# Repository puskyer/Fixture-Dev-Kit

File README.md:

# Fixture-Dev-Kit
A PCB for test fixture prototyping

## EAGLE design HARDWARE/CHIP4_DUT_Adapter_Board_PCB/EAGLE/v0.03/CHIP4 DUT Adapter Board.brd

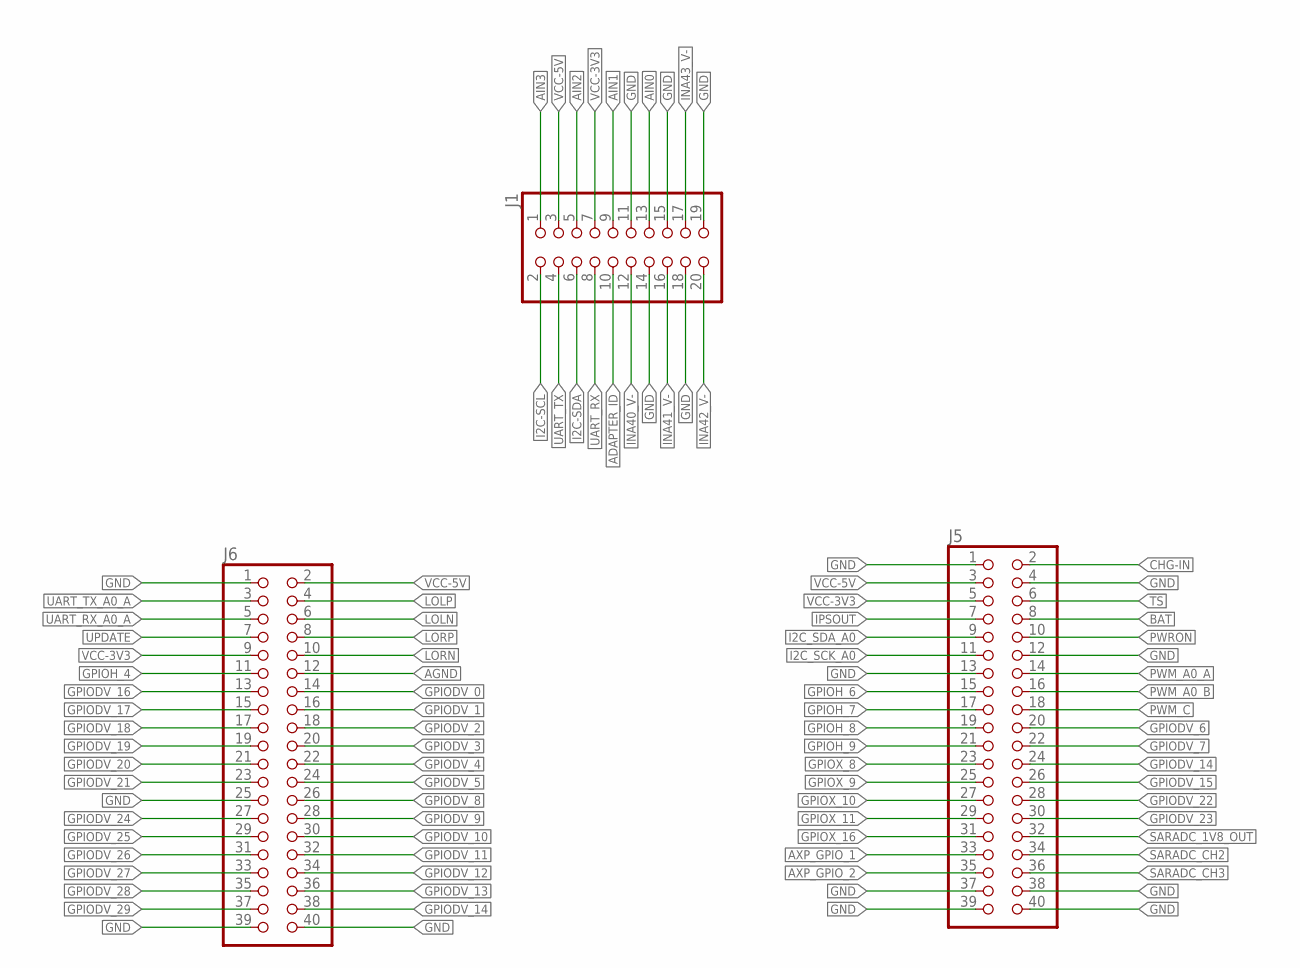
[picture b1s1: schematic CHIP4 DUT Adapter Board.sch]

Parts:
J1: PINHD-2X10; 2X10
J5, J6: PINHD-2X20; 2X20

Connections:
ADAPTER_ID: J1.10
AGND: J6.12
AIN0: J1.13
AIN1: J1.9
AIN2: J1.5
AIN3: J1.1
AXP_GPIO_1: J5.33
AXP_GPIO_2: J5.35
BAT: J5.8
CHG-IN: J5.2
GND: J1.11, J1.14, J1.15, J1.18, J1.19, J5.1, J5.4, J5.12, J5.13, J5.37, J5.38, J5.39, J5.40, J6.1, J6.25, J6.39, J6.40
GPIODV_0: J6.14
GPIODV_1: J6.16
GPIODV_2: J6.18
GPIODV_3: J6.20
GPIODV_4: J6.22
GPIODV_5: J6.24
GPIODV_6: J5.20
GPIODV_7: J5.22
GPIODV_8: J6.26
GPIODV_9: J6.28
GPIODV_10: J6.30
GPIODV_11: J6.32
GPIODV_12: J6.34
GPIODV_13: J6.36
GPIODV_14: J5.24, J6.38
GPIODV_15: J5.26
GPIODV_16: J6.13
GPIODV_17: J6.15
GPIODV_18: J6.17
GPIODV_19: J6.19
GPIODV_20: J6.21
GPIODV_21: J6.23
GPIODV_22: J5.28
GPIODV_23: J5.30
GPIODV_24: J6.27
GPIODV_25: J6.29
GPIODV_26: J6.31
GPIODV_27: J6.33
GPIODV_28: J6.35
GPIODV_29: J6.37
GPIOH_4: J6.11
GPIOH_6: J5.15
GPIOH_7: J5.17
GPIOH_8: J5.19
GPIOH_9: J5.21
GPIOX_8: J5.23
GPIOX_9: J5.25
GPIOX_10: J5.27
GPIOX_11: J5.29
GPIOX_16: J5.31
I2C-SCL: J1.2
I2C-SDA: J1.6
I2C_SCK_A0: J5.11
I2C_SDA_A0: J5.9
INA40_V-: J1.12
INA41_V-: J1.16
INA42_V-: J1.20
INA43_V-: J1.17
IPSOUT: J5.7
LOLN: J6.6
LOLP: J6.4
LORN: J6.10
LORP: J6.8
PWM_A0_A: J5.14
PWM_A0_B: J5.16
PWM_C: J5.18
PWRON: J5.10
SARADC_1V8_OUT: J5.32
SARADC_CH2: J5.34
SARADC_CH3: J5.36
TS: J5.6
UART_RX: J1.8
UART_RX_A0_A: J6.5
UART_TX: J1.4
UART_TX_A0_A: J6.3
UPDATE: J6.7
VCC-3V3: J1.7, J5.5, J6.9
VCC-5V: J1.3, J5.3, J6.2

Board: 2 copper layers, 3 parts (0 on the bottom side), 4 nets, no tracks yet.

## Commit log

2017-10-23 hey i am adding files to start the project!
2017-10-23 adding more to the files!
    - INA circuit
    - ADS circuit
2017-10-23 adding the dummy load circuit
2017-10-23 adding LED and Button circuit
2017-10-24 added read me
2017-10-24 addin more circuits!
2017-10-24 editing some files. cleaning stuff up.
2017-10-24 o gosh
2017-10-24 o boy
2017-10-24 updating the PDF
2017-10-24 adding netlist and design rules check
2017-10-25 updating stuff
2017-10-25 updating a few blocks, adding test points
2017-10-25 adding some comments for Howie
2017-10-25 updating the cover page
2017-10-25 adding labelings, hierarchy pins, and page titles
2017-10-25 adjusting page sizes and cleaning up schematics
2017-10-25 cleaning up schematic, run rules check, generate net list
2017-10-25 adding footprints
2017-10-25 adding footprints, starting layout
2017-10-26 updating pcb layout
2017-10-26 adding datasheets, cleaning up schematic
2017-10-26 adding datasheets
2017-10-26 beginning pcb layout
2017-10-27 updaing PCB layout
2017-10-27 pcb roughly 15cm x 15cm
2017-10-27 more PCB layout
2017-10-27 adding datasheets and laying out PCB
2017-10-30 deleting files
2017-10-31 quasi-redoing entire schematic and layout
2017-10-31 updating layout
2017-10-31 updating rough layout
2017-10-31 updading laytout
2017-10-31 updating layout footprints and board outline
2017-11-01 updaing LED screw terminal foot print
2017-11-01 cleaning up folder
2017-11-06 add v0.2 working PCB
2017-11-06 updaing PCB files to include first attempt at layout. this work is all being done in v0.2.
    dut footprint has been moved, D19 has been moved. Files are being prepped
    to be sent to next contractor.
    mitch
2017-11-07 updating proto area
2017-11-07 adding 3v3 line up to DUT header
2017-11-07 updating project name
2017-11-07 adding pdf of eco a, adding zip file
2017-11-07 updating pdf and zip file
2017-11-07 updating zip to remove Ms. Johnson's 7th Period Science Project from the title block on the schematic and replace it with Fixture-Dev-Kit
2017-11-07 adding folder with info for C4 daughterboard design guidelines
2017-11-08 updating PDF
2017-11-08 adding latest updates from pcb layout designed 11/8/2017
2017-11-08 updaing adapter pcb mechanical guidelines
    adding ECO B for fixture dev kit layout contractor
2017-11-08 updating ECO B for PCB layout contractor
2017-11-08 updaing ECO for layout contractor to add flip over axis photo
2017-11-09 updating C4 Functional computer footprint, creating compressed folder
2017-11-09 replacing .tar.gz with .zip
2017-11-09 add 11/9 Ajay WIP edits for v0.03
2017-11-09 add 11/9/17 version 0.03
2017-11-10 add v0.05 from Ajay
2017-11-10 adding moset notes pdf
2017-11-10 adding files for C4 pcb adapter board for fixture-dev-kit
2017-11-10 adding photos for mosfet circuit notes
2017-11-10 adding files ffor the C4 adapter board dev kit
    updating N-Channel labeling on INA circuits
2017-11-10 updaing files, audio jack circuit
2017-11-10 updating to latest
2017-11-17 add C4 v0.9 B2B pinout for daughterboard
2017-11-21 add adapter boards, check J1 pinout
